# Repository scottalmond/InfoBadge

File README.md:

# InfoBadge
Low power wearable badge for quick-access information without wireless connectivity

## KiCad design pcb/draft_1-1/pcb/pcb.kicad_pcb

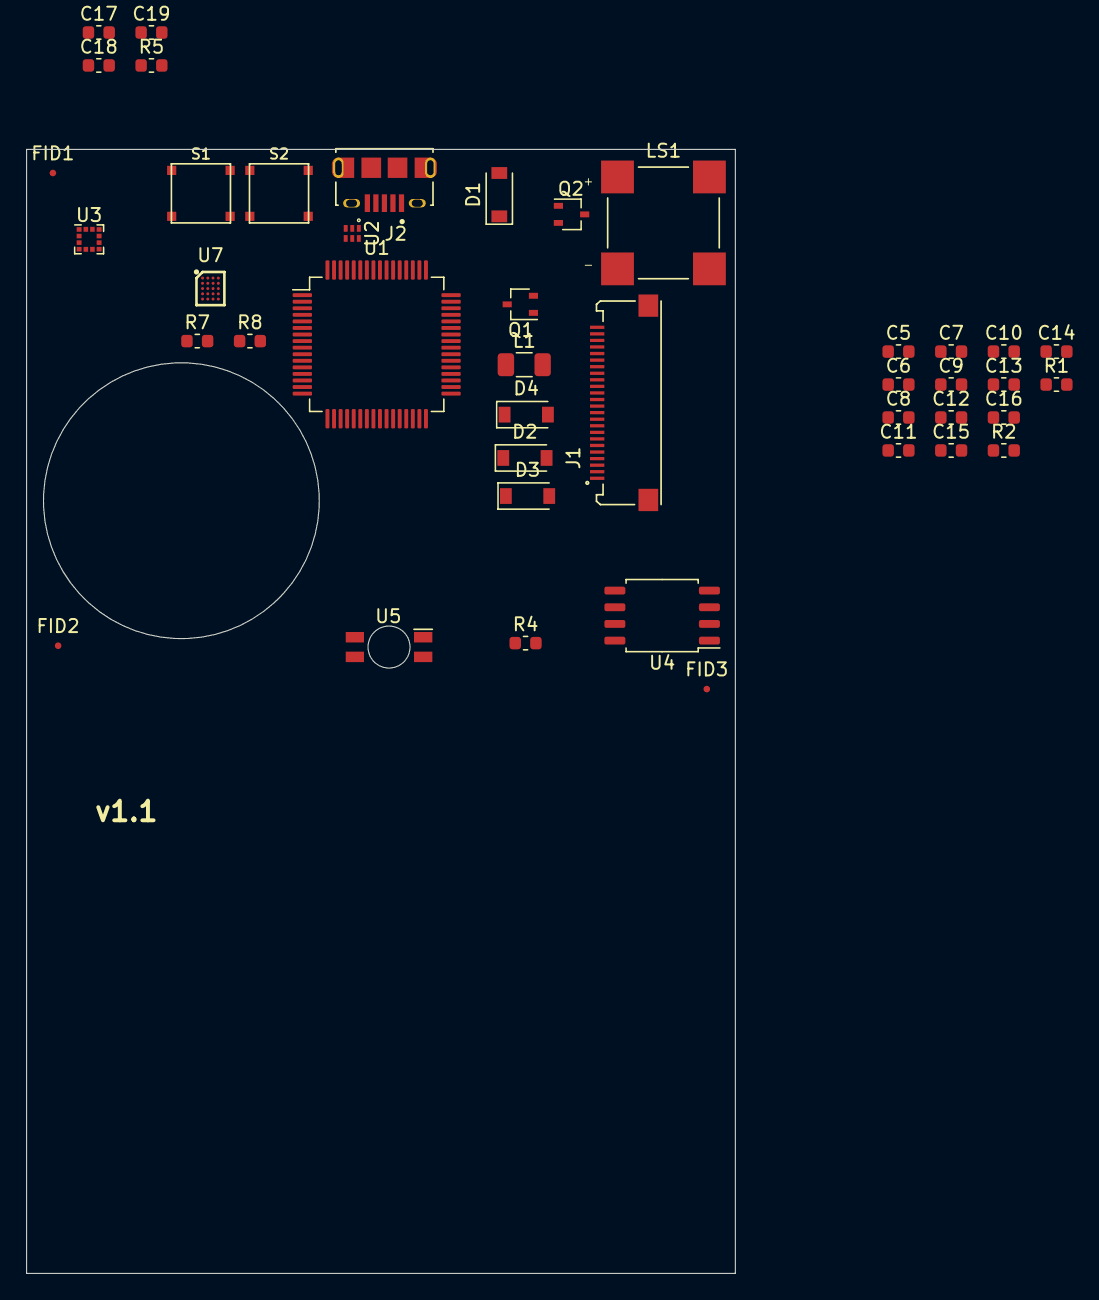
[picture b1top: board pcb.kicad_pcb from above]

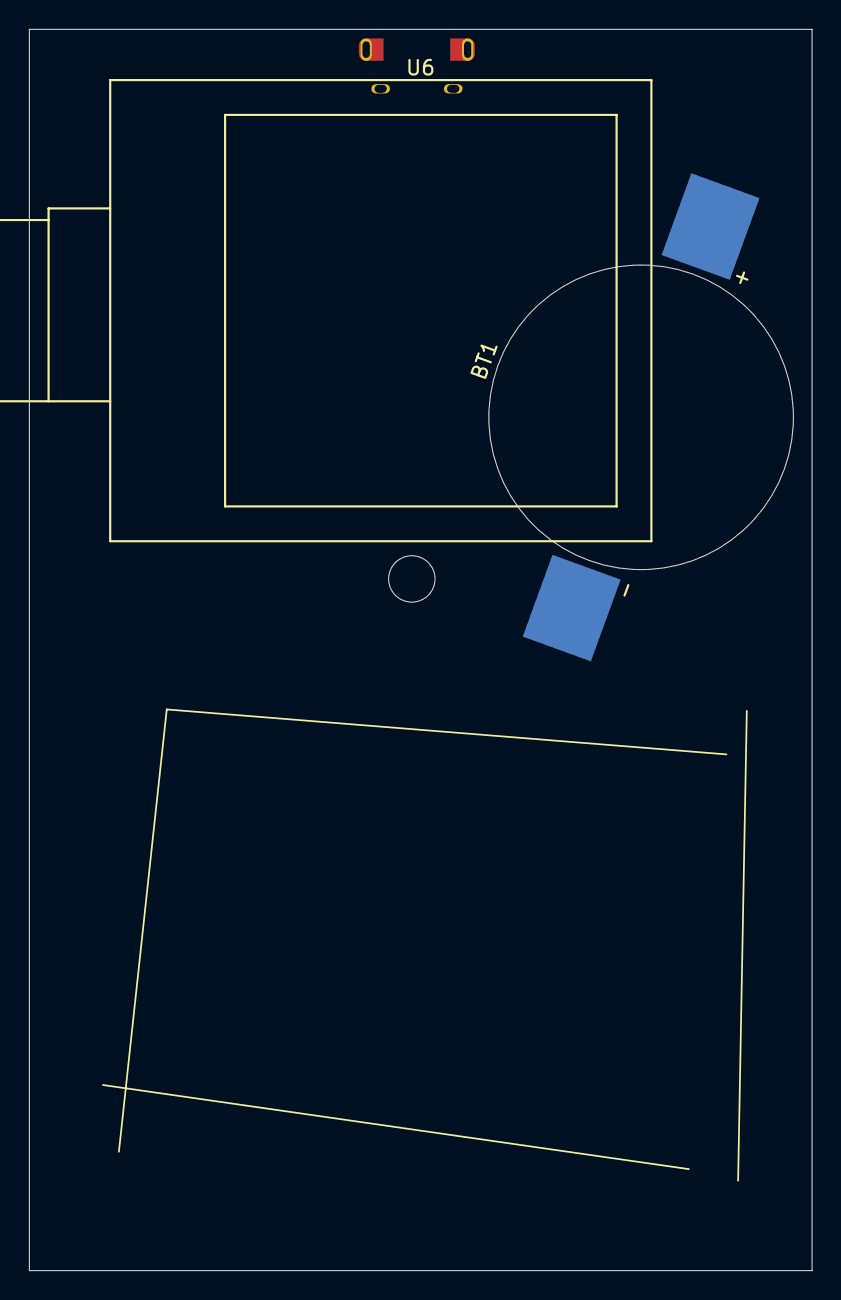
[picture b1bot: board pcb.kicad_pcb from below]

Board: 2 copper layers, 54.0 x 85.6 mm, 44 parts (2 on the bottom side), 33 nets, no tracks yet.

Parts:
BT1: 45mAh; LIR2032
C5, C6, C8, C9, C10, C11, C12, C13, C14: 1uF; C_0603_1608Metric
C7: 100nF; C_0603_1608Metric
C15, C16: 4.7uF; C_0603_1608Metric
C17: 22uF; C_0603_1608Metric
C18, C19: 10uF; C_0603_1608Metric
D1, D2, D3, D4: MBR0530; D_SOD-123
FID1, FID2, FID3: Fiducial; Fiducial_0.5mm_Mask1mm
J1: XF2M-2415-1A; OMRON_XF2M-2415-1A
J2: 10118194-0001LF; AMPHENOL_10118194-0001LF
L1: 68uH; L_1206_3216Metric
LS1: CMT-8503-90-SMT-TR; XDCR_CMT-8503-90-SMT-TR
Q1, Q2: SI1308EDL-T1-GE3; SOT-323_SC-70
R1, R5, R7, R8: 10k; R_0603_1608Metric
R2: 3R0; R_0603_1608Metric
R4: 68R0; R_0603_1608Metric
S1, S2: TL3315NF100Q
U1: ATSAML21J18B-AUT; TQFP-64_10x10mm_P0.5mm
U2: TPD4S012DRYR; SON50P100X145X60-6N
U3: IIS2DLPC; LGA-12_2x2mm_P0.5mm
U4: AT25SF641; SOIC-8_5.275x5.275mm_P1.27mm
U5: XZMDKCBDDG45S-9; PLCC-4
U6: eInk_waveshare_1.54A
U7: BQ25155; BGA20C40P4X5_162X202X50

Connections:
+1V8: C19.2, R5.2, R7.1, R8.1, U3.9, U3.10, U7.D1, U7.E1
+3V3: C7.1, C15.1, C18.2, D1.1, J1.15, J1.16, L1.2, LS1.P, U4.8, U5.2, U7.D4
+5V: J2.1, U2.6, U7.A1
D+: J2.3, U1.46, U2.2
D-: J2.2, U1.45, U2.1
INT_PG: R5.1, U7.B1
unnamed: U7.A3, U7.B3
unnamed: J2.S1, J2.S2, J2.S3, J2.S4, J2.S5, J2.S6
unnamed: C5.1, J1.4
unnamed: C6.1, J1.5
unnamed: C8.1, J1.18
unnamed: C9.1, J1.19
unnamed: C10.1, J1.20
unnamed: C12.1, J1.22
unnamed: C14.1, J1.24
unnamed: C16.1, D2.2, L1.1, Q1.3
unnamed: C16.2, D3.1, D4.2
unnamed: C17.2, U7.A2, U7.B2, U7.E4
unnamed: D1.2, LS1.N, Q2.3
unnamed: J2.4, U2.3
unnamed: R4.2, U5.1
unnamed: S1.1, S1.2, U7.C1
unnamed: S2.1, S2.2
unnamed: S2.3, S2.4
unnamed: U1.21, U1.34, U1.48
SCL_1V8: R8.2, U1.60, U3.1, U7.E3
SDA_1V8: R7.2, U1.59, U3.4, U7.E2
eBS: C5.2, C6.2, C7.2, C8.2, C9.2, C10.2, C11.2, C12.2, C13.2, C14.2, C15.2, C17.1, C18.1, C19.1, D4.1, J1.8, J1.17, J2.5, Q2.2, R1.2, R2.2, S1.3, S1.4, U1.7, U1.22, U1.33, U1.47, U1.54, U2.4, U3.5, U3.6, U3.7, U3.8, U4.4, U7.A4, U7.B4, U7.C3, U7.C4
eDIN: J1.14, U4.2
eGDR: J1.2, Q1.1, R1.1
ePREVGH: C11.1, D2.1, J1.21
ePREVGL: C13.1, D3.2, J1.23
eRESE: J1.3, Q1.2, R2.1

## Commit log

2019-12-10 concept draft
2019-12-18 more research
2020-02-09 minor edits
2020-02-11 paper cut out trade study
2020-02-15 paper cutout study
2020-02-17 trade study on speaker
2020-02-19 heelo world attempt
2020-02-23 experimenting with usb serial, DAC and GPO
2020-03-11 adding schematic
